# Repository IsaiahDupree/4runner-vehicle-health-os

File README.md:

# 4Runner Vehicle Health OS

Local-first, explainable vehicle-health and maintenance software for a 2005 Toyota 4Runner.

The project has two immutable source baselines: [Vehicle Health OS PRD v0.1](docs/prd/2005_Toyota_4Runner_Vehicle_Health_OS_PRD_v0.1.docx) and [Telemetry Build Master Spec v1](docs/prd/4Runner_Telemetry_Build_Master_Spec.docx). Their joined authority and unique requirement namespaces are defined in the [master project specification](docs/prd/MASTER-PROJECT-SPEC.md). The later [focused A/C telemetry source record](docs/prd/AC-TELEMETRY-SOURCE.md) controls the A/C node where it is more specific. The governing invariant is:

> raw observation -> decoded signal -> feature -> versioned equation -> calculation run -> finding -> recommendation -> service/inspection -> new lifecycle baseline

No derived value is authoritative unless that lineage can be reconstructed.

## Rev I lighting controller and voltage monitor

The [single-board Rev I hardware](hardware/console-led-node-v0.1/pcb-rgbw-revi/README.md)
adds protected ACC supply-voltage sensing to the existing six-wire Toyota inlet,
with revised native PCB, enclosure assembly, factory BOM and verification evidence.
The [WLED workspace](firmware/console-led-revg/CONFIGURATION.md) includes the actual
phone/head-unit UI, calibrated vehicle inputs and the existing CAN gateway's
foreground iPhone relay. It measures the switched feed at the box; ACC-off resting
battery monitoring is unavailable. Physical and vehicle qualification remain pending.

## Native iPhone lighting app

The [4Runner Lighting app](ios/Lighting/README.md) provides WLED-style color-wheel,
effect, segment and controller-preset controls. Config contains the existing CAN
relay, Rev I voltage monitor and Toyota input settings. It uses the current
single analog RGBW output zone.

The [4Runner WLED Integration skill](skills/4runner-wled-integration/SKILL.md)
preserves the approved interface, six-wire architecture, PCB/CAD and JLCPCB cost
lessons, with links to the actual test and delivery evidence.

## Rev H lighting controller

The [screw-terminal revision](hardware/console-led-node-v0.1/pcb-rgbw-revh/README.md)
uses one integrated PCB, six factory-soldered terminal blocks, a six-wire
Toyota inlet and a five-wire RGBW outlet. The gland-to-terminal wire paths,
support rails, fasteners and factory assembly files are included. It remains
an evaluation design requiring physical and vehicle qualification.

## Rev G media snapshot

The [single-board RGBW controller](hardware/console-led-node-v0.1/pcb-rgbw-revg/README.md)
includes the PCB, gland enclosure, inline Toyota power harness and WLED relay
integration. [Studio pictures and the narrated 3D demonstration](hardware/console-led-node-v0.1/pcb-rgbw-revg/presentation/README.md)
show its exterior, installed electronics, component layout and service assembly.
This is an evaluation prototype; physical electrical, sealing and vehicle-fit
acceptance remain pending.
[Download the video, CAD kits and 3D source](https://github.com/IsaiahDupree/4runner-vehicle-health-os/releases/tag/revg-studio-2026-11-21).

## Current baseline

E0 plus the first native iOS control slice are implemented here:

- stable typed domain IDs;
- versioned JSON Schemas for evidence, signals, captures, equations, calculations, and AI claims;
- a protobuf source contract and fixed transport-frame decision for mobile/ESP32 interoperability;
- deterministic simulator capture bundles with hashes and manifests;
- an A/C bench-sweep capture/replay path, A/C node telemetry and POST contracts, and evidence-bound pressure-lift, pressure-ratio, and vent-delta calculations;
- offline replay with integrity, sequence, timestamp, and schema validation;
- a versioned passive-CAN discovery analyzer that reports acquisition facts, sampling coverage,
  raw activity, checksum candidates, and correlations without assigning unverified vehicle meanings;
- a source-pinned 2005 4Runner passive-CAN hypothesis pack and real-corpus evaluator that exposes
  candidate fields, conflicting transforms, limitations, and validation gates while keeping the
  accepted signal count at zero;
- an immutable eight-session/5,176-record real-CAN replay corpus with SHA-256 provenance, clean and
  faulted live/history reconstruction, and production-decoder load tests in Python, Swift, and Kotlin;
- self-resynchronizing mobile stream decoders that surface discarded/corrupt transport bytes and
  recover later valid frames without converting communication faults into vehicle-health claims;
- a canonical 15-scenario real-evidence reliability matrix covering 20-cycle soak, MTU churn,
  bursts, duplicates, loss, corruption, reordering, stale link epochs, reconnects, modeled
  supervision timeout, queue overrun, bounded memory, and mixed interference, with aligned Swift
  transport tests and a full Kotlin/on-head-unit implementation;
- per-ECU SAE J1979 supported-PID enumeration, pinned standard read-only value decoding, and an
  iPhone/Android passive-response path that cannot substitute zero for unavailable evidence;
- synchronized Techstream/reference capture plus a candidate-only analyzer for `0x2C4`, `0x025`,
  and `0x2C1` raw fields;
- deterministic passive-CAN archive offload/reload plus an iOS multi-session research chart that
  plots retained evidence, pins pack/hash/validation lineage, and fails closed across app restarts;
- a durable iPhone private-evidence outbox and authenticated append-only receiver/agent claim queue;
- local checks for schema validity and deterministic replay;
- a Swift 6 core with CRC32C framing, guarded discovery plans, signed firmware verification, OTA preflight, and AI evidence handoff;
- a buildable native SwiftUI app with handshake-verified CoreBluetooth restoration,
  encrypted-bond reconnection, WiCAN factory detection, gateway health, signed semantic experiments,
  private-network OTA, and evidence export;
- a local-first technician diagnostic-case workspace with immutable revisions, typed evidence and
  hypotheses, hash-verified private attachments, verification/void history, and deterministic
  privacy-selected draft reports that cannot mutate canonical maintenance history;
- a signed public Release Hub consumed by iPhone and Android for target-aware Android, OBD ESP32,
  and A/C recovery artifact discovery and verified staging;
- a public WiCAN Pro ESP32-S3 firmware fork with passive/listen-only enforcement, framed BLE health reporting, OTA A/B partitions, and rollback self-tests;
- a physically targeted classic-ESP32/MrDIY firmware with bonded BLE health, passive CAN, persistent
  evidence, A/B rollback, a release-default-off status SoftAP, and explicitly activated signed Wi-Fi
  OTA;
- a backup-first public Web Serial provisioner with target detection, full-flash recovery download, release hashing, installation, and same-capacity restore;
- explicit iOS, legacy Android, gateway firmware, and added-sensor hardware boundaries.

No target-vehicle PID, threshold, service interval, or trim-specific constant is invented in this baseline. Those enter only through independently validated, versioned Vehicle Signal and Configuration Packs.

## Quick start

Requires Python 3.12 or newer.

```bash
python3 -m venv .venv
.venv/bin/python -m pip install -e './tooling[test]'
.venv/bin/vhos contracts check
.venv/bin/vhos simulate --scenario cold-start-idle --output build/captures/cold-start-idle
.venv/bin/vhos validate-bundle build/captures/cold-start-idle
.venv/bin/vhos replay build/captures/cold-start-idle
.venv/bin/vhos simulate --scenario ac-bench-sweep --output build/captures/ac-bench-sweep
.venv/bin/vhos validate-bundle build/captures/ac-bench-sweep
.venv/bin/vhos calculate-ac build/captures/ac-bench-sweep
.venv/bin/vhos discover-can path/to/passive-can-recent-logs.ndjson \
  --output build/can-discovery.report.json
.venv/bin/vhos evaluate-can-hypotheses \
  test-replay/real-can-2026-08-18/sessions \
  --output build/can-signal-hypotheses.report.json
.venv/bin/vhos validate-can-replay-corpus test-replay/real-can-2026-08-18
.venv/bin/vhos replay-can-corpus test-replay/real-can-2026-08-18 \
  --mode live --repeat 20 --fault clean
.venv/bin/vhos replay-can-corpus test-replay/real-can-2026-08-18 \
  --mode history --fault drop-fragment --fault-interval 257
.venv/bin/vhos test-link-reliability test-replay/real-can-2026-08-18 \
  --soak-cycles 20 --output build/link-reliability-matrix.json
.venv/bin/vhos decode-j1979 path/to/j1979-responses.ndjson \
  --supported-output build/j1979-supported.json \
  --samples-output build/j1979-standard-samples.ndjson
.venv/bin/vhos correlate-can-reference \
  --can path/to/passive-can.ndjson \
  --reference path/to/synchronized-reference-samples.csv \
  --output build/can-reference-candidates.json
.venv/bin/python -m pytest
```

The simulator namespace is deliberately separate from live vehicle data. It creates deterministic engineering evidence for automated tests; it never represents itself as a Toyota measurement.

## Gateway provisioning

- Signed release catalog: [VHOS Release Hub](https://github.com/IsaiahDupree/4runner-vhos-release-hub/releases/latest)
- Public installer: [VHOS Gateway Provisioner](https://vhos-gateway-provisioner.isaiahdupree.chatgpt.site)
- Public firmware source: [IsaiahDupree/4runner-vhos-firmware](https://github.com/IsaiahDupree/4runner-vhos-firmware)
- Development release and recovery evidence: [v0.1.0-dev.1](https://github.com/IsaiahDupree/4runner-vhos-firmware/releases/tag/v0.1.0-dev.1)
- Hardware/software baseline: [recommended hardware](docs/hardware/RECOMMENDED-HARDWARE.md) and [software baseline](docs/hardware/SOFTWARE-BASELINE.md)
- SoftAP incident and default-off activation decision: [2026-08-16 record](docs/development/ESP32-SOFTAP-ACTIVATION-INCIDENT-2026-08-16.md)
- One-command pre-car contracts/build/reset/app-death suite and true-power boundary: [BLE fault-injection plan](docs/development/BLE-FAULT-INJECTION-TEST-PLAN.md)
- Capture-export disconnect and dev28/dev29 recovery: [2026-08-18 incident](docs/development/BLE-CAPTURE-SYNC-DISCONNECT-INCIDENT-2026-08-18.md)

The first installation and recovery path uses a desktop Chrome or Edge browser, USB-C data, and Web
Serial. The browser requires a full-flash backup before it installs the merged image. The iPhone OTA
software path is implemented, but vehicle installation remains locked until deterministic PARKED
and gateway-supply evidence plus the physical backup/upload/power-loss/rollback/restore matrix pass.
See [iPhone to ESP32 Wi-Fi OTA](docs/development/IPHONE-TO-ESP32-WIFI-OTA.md).
The stable device labels and separation from transport identifiers are defined in
[the device naming contract](docs/development/DEVICE-NAMING-CONTRACT.md).

## Repository map

| Path | Responsibility |
| --- | --- |
| `docs/prd/` | Immutable product baseline and source integrity record |
| `docs/architecture/decisions/` | Accepted technical decisions and invariants |
| `contracts/jsonschema/v1/` | Authoritative serialized domain contracts |
| `contracts/proto/v1/` | Mobile/ESP32 payload source contract |
| `equations/v1/` | Immutable A/C equation definitions with applicability and truth boundaries |
| `tooling/` | Contract validator, simulator, bundle writer, and replay engine |
| `tests/` | Contract, determinism, corruption, ordering, and replay tests |
| `test-replay/` | Immutable real-capture corpora and cross-platform replay provenance |
| `ios/` | Native iOS app, portable Swift core, and deterministic XcodeGen project |
| `web-flasher/` | Public backup-first ESP32-S3 installer and recovery UI |
| `android/` | Preserved original Android module boundary; not the primary client after ADR-0003 |
| `firmware/` | Shared ESP32 component boundaries and read-only safety policy |
| `vehicle-signal-packs/` | Accepted signal/configuration packs plus separately contracted, discovery-only hypothesis packs that cannot feed owner health |

Related public repositories keep runtime ownership separate: Android head unit
[`4runner-vhos-android`](https://github.com/IsaiahDupree/4runner-vhos-android) ([download the current `0.1.0-dev.16` APK](https://github.com/IsaiahDupree/4runner-vhos-android/releases/download/android-v0.1.0-dev.16/app-debug.apk)), OBD firmware
[`4runner-vhos-firmware`](https://github.com/IsaiahDupree/4runner-vhos-firmware), A/C firmware
[`4runner-ac-telemetry-node`](https://github.com/IsaiahDupree/4runner-ac-telemetry-node), and the
signed catalog/portal [`4runner-vhos-release-hub`](https://github.com/IsaiahDupree/4runner-vhos-release-hub).

## Development order

1. E1: iOS append-only local truth store and lifecycle ledger; the gateway contract client is now scaffolded.
2. E2: physically verify the published WiCAN Pro VHOS foundation, then add passive capture and constrained discovery without widening the transmit boundary.
3. E3: iOS ingest, reconnect/deduplication, raw persistence, and replay adapter.
4. E4: verified generic OBD baseline plus target-vehicle signal discovery and validation.
5. E5/E6: maintenance schedule and equation/lineage engines before owner-facing scoring.

See [E0 implementation record](docs/delivery/E0-IMPLEMENTATION.md) for the exact backlog and acceptance mapping.
The current saved-vehicle evidence and strict UI interpretation boundary are recorded in the
[CAN discovery display baseline](docs/development/CAN-DISCOVERY-DISPLAY-BASELINE-2026-08-18.md).
The device-free sustained-load, corruption, fragmentation, disconnect, and Android historical
replay workflow is recorded in
[the real-CAN replay record](docs/development/REAL-CAN-REPLAY-AND-LOAD-TESTING-2026-08-18.md).
The 15-condition cross-device impairment matrix, acceptance budgets, Android reliability UI, and
remaining hardware-in-loop gates are recorded in
[the cross-device reliability lab](docs/development/CROSS-DEVICE-RELIABILITY-LAB-2026-08-18.md).
The supported-PID, synchronized Toyota-reference, and private-outbox implementation is recorded in
[the August 18 J1979/evidence delivery](docs/development/J1979-REFERENCE-VALIDATION-AND-PRIVATE-OUTBOX-2026-08-18.md).
The current source-pinned Toyota signal candidates, corpus results, interpretation boundaries, and
minimum validation session are recorded in
[the CAN signal interpretation record](docs/development/CAN-SIGNAL-INTERPRETATION-2026-08-18.md).
The latest iPhone-export verification, primary-source research update, candidate ranking, Android
display boundary, and next labeled-capture procedure are recorded in
[the 2026-08-20 CAN evidence and research update](docs/development/CAN-EVIDENCE-RESEARCH-UPDATE-2026-08-20.md).
The real-evidence iPhone chart, fresh-session archive reload gate, exact candidate fields, and
owner-health authority lock are recorded in
[the iOS retained CAN research implementation](docs/development/IOS-RETAINED-CAN-RESEARCH-GRAPHS-2026-08-20.md).
The play/pause/scrub/speed/loop transport, progressive exact-point graph, session-boundary display,
and real multi-session acceptance suite are recorded in
[the iOS retained CAN playback lab](docs/development/IOS-RETAINED-CAN-PLAYBACK-LAB-2026-08-20.md).

The authority-separated physical-unit candidates, derived statistics, rotational comparison, and
cross-platform presentation rules are recorded in [the CAN units view](docs/development/CAN-UNITS-NOTE-2026-08-28.md).

The authority boundary and delivered local iOS technician workflow are recorded in
[ADR-0005](docs/architecture/decisions/0005-technician-diagnostic-case-drafts.md) and the
[mechanic diagnostic-case implementation record](docs/development/MECHANIC-DIAGNOSTIC-CASE-MVP-2026-09-07.md).

Run the complete copied-iPhone evidence recovery, delta analysis, candidate
mapping, replay, and 15-scenario link stress lab with one command using
[the offline field-return runbook](docs/development/OFFLINE-FIELD-RETURN-ONE-SHOT.md).
Run that analysis together with all shared, Swift/iOS Simulator, and Android
desktop gates—without contacting any physical device—using
[the device-free field-return acceptance runner](docs/development/DEVICE-FREE-FIELD-RETURN-ACCEPTANCE.md).
The governing unknown-by-default whole-vehicle model, head-unit inventory contract, 2005 4Runner
configuration guard, and evidence-basis separation are recorded in
[the whole-vehicle digital-twin foundation](docs/development/WHOLE-VEHICLE-DIGITAL-TWIN-FOUNDATION-2026-08-18.md).
The cross-platform Connect → Discover → Test → Capture → Validate → Promote workflow, platform
roles, authority states, session records, fail-closed promotion gate, and first production slice are
defined in
[the Discovery subsystem architecture](docs/development/DISCOVERY-SUBSYSTEM-ARCHITECTURE-2026-08-21.md).
The Android vendor-stack discovery fallback, one-client iPhone/Android handoff, connected-launch
recovery, and explicitly owner-acknowledged local evidence-only selector workflow are recorded in
[the BLE/local-evidence runbook](docs/development/BLE-DISCOVERY-CONNECTED-LAUNCH-AND-LOCAL-EVIDENCE-2026-08-24.md).
The exact offline capture-finalization and experimental-candidate persistence boundary—and the
remaining reason the registration button stays disabled—are recorded in
[the offline candidate-registration gap](docs/development/OFFLINE-CANDIDATE-REGISTRATION-GAP-2026-08-24.md).

## Safety boundary

- Production gateway startup is passive/listen-only.
- There is no arbitrary CAN-transmit command in the shared contract.
- Any diagnostic request references a firmware-resident allowlist entry; iOS does not supply raw request bytes.
- Active Tests, vehicle control, ECU flashing, and code clearing are outside MVP scope.
- Gateway health/data loss is never presented as vehicle failure.

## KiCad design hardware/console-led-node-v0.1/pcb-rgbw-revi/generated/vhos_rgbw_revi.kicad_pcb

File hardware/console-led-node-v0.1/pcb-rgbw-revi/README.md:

# Rev I: protected switched-supply voltage sensing

Rev I adds on-board sensing of **ACC_FUSED**, after the main fuse and before the input eFuse. The same six-wire Toyota inlet remains the only power source. ACC-off resting battery measurements are unavailable. This is a voltage monitor for the supply at the box, not a state-of-charge meter or a battery-post measurement.

The existing SN3257-Q1 switch has unused channels. Channel 3 now connects VOLT_CLAMP at U5 pin 10 to VOLT_SW at pin 9 when CHIP_EN is valid; its alternate input stays grounded. The new path reuses the exact Rev H protected TAIL/DIM network and goes to ESP32-S3 GPIO1 / U11 pad 39. The remaining switch channel and the Toyota reserve wires stay unused.

| Added references | Existing part reused | Quantity |
|---|---|---:|
| R40, R41 | RT1206BRD0749K9L, 49.9k 0.1% | 2 |
| R42, R44 | 0603WAF2202T5E, 22k 1% | 2 |
| R43 | 0603WAF1802T5E, 18k 1% | 1 |
| U12 | LM4040C25QFTA, 2.5 V automotive shunt clamp | 1 |
| D10 | NSVBAT54HT1G, negative clamp | 1 |
| C32 | CC0603KRX7R9BB104, 100 nF 50 V | 1 |

This adds **eight populated positions, zero unique manufacturer SKUs**. At the retained November 21 JLCPCB snapshot, the material increment is **$0.8485**, making nominal PCB component material **$24.4326**. It is not a fresh checkout quote or finished-product price. Existing holder/clamp stock limitations, supplier assembly, fabrication, box build, firmware programming and testing remain separate. All parts are factory fitted.

The nominal ADC gain is 0.0684815; a 14.4 V input produces approximately 0.986 V at the ADC. A 32-corner resistor screen gives approximately 0.971–1.002 V, excluding switch, ADC, temperature and other errors. Firmware labels nominal conversion as an **uncalibrated estimate** until two meter-referenced bench points are applied. The shunt clamp saturates the transfer above its linear range; this is not a wide-range automotive pulse recorder.

[voltage_screen.py](voltage_screen.py) checks the actual selected manufacturer identities and resistor tolerances. Its clamp bounds are explicitly conditional assumptions inherited from the existing sensing design, not physical pulse evidence. Factory calibration, reset/isolation, negative-pulse behavior, resistor/clamp energy and voltage accuracy still need bench verification.

The accepted native Rev I board keeps the Rev H 133 x 65 mm outline, terminal locations and mounting positions, and adds the sensing parts in the existing free component area. Orion completed native routing with zero reported ERC, DRC, unconnected-net or schematic-parity findings under the retained project rules. The populated board passed 497 enclosure/wire checks, eight insert/driver access axes and three offline slices with supports disabled and zero support segments. The prior Rev H kit remains a separate frozen artifact.

| Revised artifact | File |
|---|---|
| Native PCB and schematic | [KiCad PCB](generated/vhos_rgbw_revi.kicad_pcb), [schematic PDF](generated/schematic.pdf) |
| Populated board geometry | [STEP](generated/routed_shield.step), [native board view](generated/board.png) |
| Complete enclosure assembly | [FreeCAD](generated/4Runner_RevI_Terminal_Assembly.FCStd), [STEP](generated/4Runner_RevI_Terminal_Assembly.step) |
| Support-free print exports | [Base STL](generated/case_base.stl), [lid STL](generated/case_lid.stl), [gland plate STL](generated/gland_plate.stl) |
| Factory assembly | [75-position BOM](jlcpcb/BOM.csv), [placement CPL](jlcpcb/CPL.csv), [Gerbers](generated/4Runner_RGBW_RevI_Gerbers.zip) |
| Wiring and provenance | [Wire register](WIRE-REGISTER.csv), [routing lengths](generated/wire-cut-routing.csv), [native verification](generated/verification.json), [test evidence](VERIFICATION.md) |

The complete product still needs the unchanged [harness and case hardware](../pcb-rgbw-revh/HARNESS-AND-CASE.csv), external inline harness and supplier box assembly/programming/testing. A BOM/CPL is factory input; it is not confirmation of JLCPCB stock, through-hole assembly acceptance or a delivered plug-and-play quote.

Software and UI behavior: [WLED/CAN/vehicle-input configuration](../../../firmware/console-led-revg/CONFIGURATION.md). Rev I firmware enables GPIO1 sense; the unmodified Rev H board must use the original target without that input.

This revision is evaluation hardware. No physical installation or manufacturing release is implied by source, static screening, a successful firmware build or digital fit checks.

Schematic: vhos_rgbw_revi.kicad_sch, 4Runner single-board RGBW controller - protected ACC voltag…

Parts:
C2, C3, C30: 2.2u 100V X7R; C_1210_3225Metric; MPN CL32B225KCJVPJE
C4: 10n 50V X7R; C_0603_1608Metric; MPN 0603B103K500NT
C13, C27, C29: 100n 100V X7R; C_0805_2012Metric; MPN CL21B104KCFNNNE
C17: 47u 50V; CP_Elec_8x6.2; MPN EEEFK1H470P
C18, C19, C20, C32: 100n 50V; C_0603_1608Metric; MPN CC0603KRX7R9BB104
C22, C23, C24, C31: 22u 25V X5R; C_1206_3216Metric; MPN CL31A226KAHNNNE
C25, C28: 100n 50V X7R; C_0603_1608Metric; MPN CC0603KRX7R9BB104
C26: 1u 50V X5R; C_0603_1608Metric; MPN CL10A105KB8NNNC
D1, D2: SMBJ28CAQ; D_SMB; MPN SMBJ28CAQ-13-F
D7, D8, D10: NSVBAT54HT1G; onsemi_SOD-323_477; MPN NSVBAT54HT1G
D9: SS56 60V 5A; D_SMA; MPN SS56
F1: 3A MINI MAIN / LED; Keystone_3568_MINI_Vertical; MPN 3568-10
F2: 1A MINI LOGIC; Keystone_3568_MINI_Vertical; MPN 3568-10
JT1: GND/ACC; KEFA_KF128_5.08_2P; MPN KF128-5.08-2P-AA
JT2: TAIL/DIM; KEFA_KF128_5.08_2P; MPN KF128-5.08-2P-AA
JT3: RSV3/RSV4; KEFA_KF128_5.08_2P; MPN KF128-5.08-2P-AA
JT4: R-/G-; KEFA_KF128_5.08_2P; MPN KF128-5.08-2P-AA
JT5: B-/+LED; KEFA_KF128_5.08_2P; MPN KF128-5.08-2P-AA
JT6: W-/NC; KEFA_KF128_5.08_2P; MPN KF128-5.08-2P-AA
L1: 22u 20% TDK; TDK_SPM6545VT-D; MPN SPM6545VT-220M-D
MH1, MH2, MH3, MH4: M3 CASE SUPPORT; MountingHole_3.2mm_M3; MPN PCB FEATURE
Q1: AO3400A; SOT-23; MPN AO3400A
R1: 8.2k 1%; R_0603_1608Metric; MPN 0603WAF8201T5E
R2, R5: 47k 1%; R_0603_1608Metric; MPN 0603WAF4702T5E
R3, R13: 10k 1%; R_0603_1608Metric; MPN 0603WAF1002T5E
R4: 150k 1%; R_0603_1608Metric; MPN 0603WAF1503T5E
R17, R18, R19, R20: 100k; R_0603_1608Metric; MPN 0603WAF1003T5E
R21: 46.4k 0.1%; R_0603_1608Metric; MPN RT0603BRD0746K4L
R22: 3.92k 0.1%; R_0603_1608Metric; MPN RT0603BRD073K92L
R24, R25, R26, R27, R40, R41: 49.9k 0.1%; R_1206_3216Metric; MPN RT1206BRD0749K9L
R28, R29, R32, R33, R42, R44: 22k 1%; R_0603_1608Metric; MPN 0603WAF2202T5E
R30, R31, R43: 18k 1%; R_0603_1608Metric; MPN 0603WAF1802T5E
R36, R37, R38: 10k; R_0603_1608Metric; MPN 0603WAF1002T5E
R39: 100k 1%; R_0603_1608Metric; MPN 0603WAF1003T5E
TP5: LED_POS; TestPoint_Pad_D1.0mm; MPN PCB FEATURE
TP6: GND; TestPoint_Pad_D1.0mm; MPN PCB FEATURE
TP7: VIN_PROT; TestPoint_Pad_D1.0mm; MPN PCB FEATURE
TP8: ENABLE_REQ; TestPoint_Pad_D1.0mm; MPN PCB FEATURE
TP9: GND; TestPoint_Pad_D1.5mm; MPN PCB FEATURE
TP10: UART_TX; TestPoint_Pad_D1.5mm; MPN PCB FEATURE
TP11: UART_RX; TestPoint_Pad_D1.5mm; MPN PCB FEATURE
TP12: BOOT_N; TestPoint_Pad_D1.5mm; MPN PCB FEATURE
TP13: CHIP_EN; TestPoint_Pad_D1.5mm; MPN PCB FEATURE
TP14: ESP_3V3; TestPoint_Pad_D1.5mm; MPN PCB FEATURE
U1: LMR51610XDBVR; SOT-23-6; MPN LMR51610XDBVR
U2: DRV8803PWPR; TI_PWP0016J; MPN DRV8803PWPR
U4: TPS26600PWPR; TI_PWP0016A; MPN TPS26600PWPR
U5: SN3257-Q1; TSSOP-16_4.4x5mm_P0.65mm; MPN SN3257QPWRQ1
U6, U7, U12: LM4040 2.5V; SOT-23; MPN LM4040C25QFTA
U10: TLV803EC30DBZR; SOT-23; MPN TLV803EC30DBZR
U11: ESP32-S3-WROOM-1-N16R2; ESP32-S3-WROOM-1; MPN ESP32-S3-WROOM-1-N16R2

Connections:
/ACC_FUSED: C13.1, C30.1, D1.1, F1.2, R2.1, R21.1, R40.1, U4.1 (IN), U4.2 (IN)
/BOOTCAP: C28.1, U1.1 (CB)
/BOOT_N: R37.2, TP12.1, U11.27 (IO0)
/CHIP_EN: C26.1, R36.2, TP13.1, U5.1 (SEL), U10.1 (RESET_N), U11.3 (EN)
/DIM_ADC: C20.1, R31.2, R33.1, U11.4 (IO4)
/DIM_CLAMP: D8.1 (K), R27.2, R29.1, U5.6 (S2B), U7.1 (K)
/DIM_RETURN: JT2.2 (DIM), R26.1
/DIM_SERIES: R26.2, R27.1
/DIM_SW: R31.1, U5.7 (D2)
/DOWNLOAD_STRAP: R38.1, U11.16 (IO46)
/EFUSE_RTN: C4.2, R1.2, R3.2, R22.2, U4.6 (MODE), U4.8 (RTN), U4.17 (EPAD)
/ENABLE_REQ: Q1.1 (G), R39.1, TP8.1, U11.23 (IO21)
/ESP_3V3: C18.1, C22.1, C23.1, C24.1, C25.1, C31.1, L1.2, R4.1, R13.1, R36.1, R37.1, TP14.1, U5.16 (VDD), U10.3 (VDD), U11.2 (3V3)
/FB_3V3: R4.2, R5.1, U1.3 (FB)
/GND: C2.2, C3.2, C13.2, C17.2, C18.2, C19.2, C20.2, C22.2, C23.2, C24.2, C25.2, C26.2, C27.2, C29.2, C30.2, C31.2, C32.2, D1.2, D2.2, D7.2 (A), D8.2 (A), D9.2, D10.2 (A), JT1.1 (GND), Q1.2 (S), R5.2, R17.2, R18.2, R19.2, R20.2, R28.2, R29.2, R32.2, R33.2, R38.2, R39.2, R42.2, R44.2, TP6.1, TP9.1, U1.2 (GND), U2.5 (GND), U2.9 (RESET), U2.12 (GND), U2.17 (EPAD), U4.9 (GND), U5.2 (S1A), U5.5 (S2A), U5.8 (GND), U5.11 (S3A), U5.12 (D4), U5.13 (S4B), U5.14 (S4A), U5.15 (EN_N), U6.2 (A), U6.3 (A/NC), U7.2 (A), U7.3 (A/NC), U10.2 (GND), U11.1 (GND), U11.40 (GND), U11.41 (EPAD), U12.2 (A), U12.3 (A/NC)
/ILIM: R1.1, U4.11 (ILIM)
/LED_B_NEG: JT5.1 (B-), U2.6 (OUT3)
/LED_EN_N: Q1.3 (D), R13.2, U2.8 (NENBL)
/LED_G_NEG: JT4.2 (G-), U2.4 (OUT2)
/LED_POS: C17.1, C27.1, D2.1, D9.1, F2.1, JT5.2 (+LED), TP5.1, U2.1 (VM), U2.2 (VCLAMP), U4.15 (OUT), U4.16 (OUT)
/LED_R_NEG: JT4.1 (R-), U2.3 (OUT1)
/LED_W_NEG: JT6.1 (W-), U2.7 (OUT4)
/OVP: R21.2, R22.1, U4.5 (OVP)
/PWM_B: R19.1, U2.11 (IN3), U11.22 (IO14)
/PWM_G: R18.1, U2.13 (IN2), U11.10 (IO17)
/PWM_R: R17.1, U2.14 (IN1), U11.11 (IO18)
/PWM_W: R20.1, U2.10 (IN4), U11.38 (IO2)
/SLEW: C4.1, U4.12 (DVDT)
/SW: C28.2, L1.1, U1.6 (SW)
/TAIL_12V: JT2.1 (TAIL), R24.1
/TAIL_ADC: C19.1, R30.2, R32.1, U11.5 (IO5)
/TAIL_CLAMP: D7.1 (K), R25.2, R28.1, U5.3 (S1B), U6.1 (K)
/TAIL_SERIES: R24.2, R25.1
/TAIL_SW: R30.1, U5.4 (D1)
/UART_RX: TP11.1, U11.36 (RXD0)
/UART_TX: TP10.1, U11.37 (TXD0)
/UVLO: R2.2, R3.1, U4.3 (UVLO)
/VEH_ACC: F1.1, JT1.2 (ACC)
/VIN_PROT: C2.1, C3.1, C29.1, F2.2, TP7.1, U1.4 (EN), U1.5 (VIN)
/VOLT_ADC: C32.1, R43.2, R44.1, U11.39 (IO1)
/VOLT_CLAMP: D10.1 (K), R41.2, R42.1, U5.10 (S3B), U12.1 (K)
/VOLT_SERIES: R40.2, R41.1
/VOLT_SW: R43.1, U5.9 (D3)

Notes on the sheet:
FUSED INPUT, REVERSE / SURGE PROTECTION AND 3.3 V SUPPLY
TOYOTA IR1 INPUT, RGBW OUTPUT AND TEST PADS
ONE COMMON-POSITIVE RGBW ZONE
TOYOTA IR1 ILLUMINATION SENSE
ONBOARD ESP32-S3, 3.3 V REGULATOR AND SERVICE PADS
EVALUATION HARDWARE / VERIFY VEHICLE FEED, LED PINOUT AND USB ISOLATION

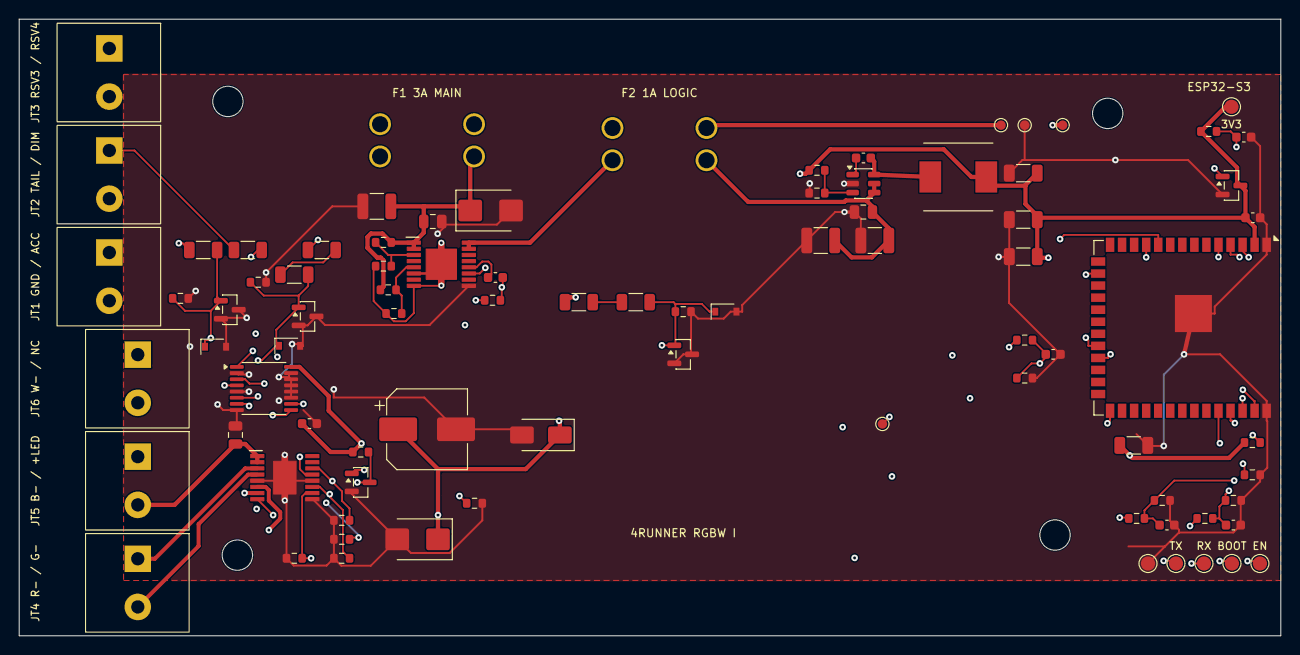
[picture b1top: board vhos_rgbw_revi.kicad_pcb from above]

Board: 4 copper layers, 133.0 x 65.0 mm, 89 parts (0 on the bottom side), 43 nets.

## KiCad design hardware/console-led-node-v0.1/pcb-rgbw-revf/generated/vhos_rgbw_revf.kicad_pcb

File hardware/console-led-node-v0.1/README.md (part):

# 2005 V8 4Runner console LED node — research and fit-check case

**Current build** [Rev G single-board controller and harness](pcb-rgbw-revg/README.md).
The photographed white six-contact Toyota harness is the box's only wired
input. The shield uses that switched 12 V and ground to power both the
ESP32-S3 and the RGBW lights. Two protected inputs read the TAIL and dimmer
circuits through the same harness. IR1-3 and IR1-4 have labeled, capped tails
at the external tee. The existing ESP32/MrDIY gateway supplies vehicle data
wirelessly. [Wire register](pcb-rgbw-revg/WIRE-REGISTER.csv).
[Project resources and fabrication files](RESOURCES.md).
Owner task: 2026-11-07. No parts ordered, functional PCB fabricated, vehicle wiring changed, or printer started.

The [earlier two-connector Rev B package](pcb-rgbw-revb/README.md) places both replaceable
fuses, reverse-battery and overvoltage protection, regulated ESP32 power and
the RGBW output on the shield. It uses one switched vehicle input and one
five-wire LED cable at the case. Its assembly instructions document that earlier population.

The earlier [RGBW Rev A package](pcb-rgbw-reva/README.md) supplies native KiCad
files, four PWM power channels, a protected logic-supply draft, a BOM and
updated case parts. Its final Orion export has zero ERC/DRC findings and zero
unfinished connections. Nominal CAD interference checks pass for the revised
assembly. The [Rev A inline harness build sheet](connector-adapter/INLINE-HARNESS.md)
retains the Toyota pass-through and earlier shield wiring. The vehicle feed,
connector fit, pod pinout, controller stack and RF fit still need physical verification.

The connector research and original inline harness record earlier evaluation
revisions. Use the current build guide for wiring the box.

## What the photographs establish

| Location | Observation and working identification | Remaining check |
| --- | --- | --- |
| Black cylindrical component at upper left | Rear of a cigarette-lighter / 12 V socket assembly | Strong visual identification; distinguish the actual socket variant by its label and front view |
| Beige connector beside that socket | Part of the local socket/illumination wiring | Function inferred from its physical routing; cavity count, mating face and part number unreadable |
| Loose white plug at lower left | Six-contact socket in the Yazaki **7283-1060** pattern. The catalog mate is **7282-1060**. Location and colors match the documented **IR1** loom | Confirm latch fit, cavity markings and electrical behavior on the truck |
| Blue connector in black switch housing at right | A console switch connection | Exact switch unidentified without its front legend; no assertion that it is DAC, differential lock or another trim-specific function |

Toyota's 2005 V8 service diagrams identify IR1 as the join between the
instrument-panel wiring and the cigarette-lighter wiring assembly. The
connector list separately identifies C6 lighter housing **90980-10760**
and C7 lamp housing **90980-11148** at the components. The photographs and
diagram support the IR1 identification. The housing fit and live ACC feed
still need checking on the truck. [IR1 pinout and harness plan](connector-adapter/IR1-WIRE-PLAN.md) ·
[Toyota connector list][ewd-connectors] · [Toyota TIS][tis].

Compare the actual mating face, latch and cavities when ordering the
pass-through parts. Match circuits by physical terminal alignment and
continuity during assembly.

## Parts that can be sourced

The complete candidate list, quantities and unresolved selection conditions are
in [BOM.csv](BOM.csv). All electronic parts are research candidates, not a
released fabrication BOM.

The [connector-to-shield research](connector-adapter/README.md) supplies the
Yazaki mating pair, the Molex PCB interface and official UNO R3 header
coordinates. The [inline harness parts list](connector-adapter/INLINE-HARNESS.md#parts)
covers the earlier Rev A cable build.

The subsequent [component CAD collection](cad-references/README.md) records six
downloaded STEP references, manufacturer versus community provenance, native
Orion inspection and the remaining Toyota/full-controller model gaps.

| Item | Concrete lead | What it establishes |
| --- | --- | --- |
| Console wiring assembly | **Toyota 82390-35010** | Dealer calls it Bulb Wire / Wiring Assembly Cigaret, center console. ToyotaPartsDeal lists 4.7 L 2UZ-FE compatibility. It may be only part of the lamp/socket loom; terminal population and both ends require a real product photo. [Dealer listing][toyota-harness], [secondary availability][harness-sale] |
| OEM socket housing | **Toyota 90980-10760** | Female housing cataloged for the lighter; not the identified mate for the loose multi-pin plug. Secondary listing currently says unavailable. [Listing][socket-housing] |
| Locking PCB connector | **Molex 43045-0600** | Six-circuit, 3 mm pitch, right-angle through-hole Micro-Fit header with PCB retention. [Manufacturer][molex-header] |
| Matching cable housing / contacts | **43025-0600 + 43030-0007** | Matching Micro-Fit family, 20–24 AWG tin socket contacts; verify insulation OD ≤1.85 mm and use the proper crimp tool. This pair fits our PCB, not Toyota's loom directly. [Housing][molex-housing], [contacts][molex-contact], [family mating catalog][molex-family] |
| Protected 5 V supply | **LM5164-Q1** | 6–100 V input, 1 A buck candidate for controller/logic. Supporting components, thermal behavior and cranking recovery remain design work. [TI][buck] |
| Reverse-battery protection | **LM74700-Q1 + suitable external N-FET** | Ideal-diode controller candidate, not a complete load-dump solution. Clamp, surge energy, FET and fuse must be designed together. [TI][ideal-diode] |
| Addressable LED data option | **SN74AHCT125-Q1** | 5 V buffer with TTL-compatible input; a possible 3.3-to-5 V data stage, not an LED power supply. [TI][level-shifter] |
| 12 V analog RGB option | **UCC27524A-Q1 + BUK9K12-60E** | Gate-driver and dual 60 V N-FET candidates; a three-channel RGB load needs enough channels, separate fusing and a reviewed thermal/current design. [TI][gate-driver], [Nexperia][mosfet] |
| Printed-case hardware | **8 × ruthex RX-M3x5.7**, **4 × M3x8**, **4 × M3x6 + insulating washers** | Case/own-carrier mounting only; not verified UNO mounting holes. [Insert manufacturer][inserts] |

Observed quotations on the research date: the Toyota wiring assembly was
$20.78 at Olathe and $14.86 with a stated 1–3 business day dispatch at
ToyotaPartsDeal. These are page observations, excluding delivery/tax and
subject to seller/VIN confirmation. No purchase has been placed.

The [earlier placement preview](pcb-preview/README.md) is superseded by the
[routed RGBW draft and native preview](pcb-rgbw-reva/README.md).

The subsequent [underbody LED comparison](led-selection/README.md) evaluates
sealed rock-light pods and an addressable strip against the owner's outdoor
mounting requirement. It recommends a DD7440 RGBW sample for evaluation; the
light and interface remain unselected. RGBW requires four power channels per
independent zone, so the earlier three-channel RGB or data-output concept is
not a final output circuit.

## Electrical and mechanical arrangement

The [Rev G bench and programming guide](pcb-rgbw-revg/BENCH.md)
covers the onboard ESP32-S3 and the 3.3 V regulator. The [Rev D two-board build](pcb-rgbw-revd/README.md)
and [shared Toyota power flow](pcb-rgbw-revb/TOYOTA-POWER-BUILD.md#power-and-lighting-leads)
record the earlier stacked version.
Check the Toyota power and ground cavities and the available current on the
truck. The case supports both captive cables at their exits.

The user identified the stacked version's controller with a product screenshot:
**ShengYang listing, purple D1 UNO ESP32-S3 N16R8 / CH340 board**. The earlier
DIYables brand assumption is superseded. Its visible UNO-style header layout
and GPIO labels agree with the seller-family reference. The new
[board identity and shield GPIO proposal](controller-board/README.md) records
that evidence, the seller dimension drawing and 32 header positions.
GPIO is a 3.3 V domain; the printed 5 V/IOREF and RST/AREF positions are not an
AVR UNO electrical pinout. Exact populated height, hole positions, power-path
behavior and final physical fit remain unverified. The original case inputs
and receipts remain frozen, with their estimated controller envelope.

The existing VHOS repository already preserves raw observations and signal
quality. Its README reports zero accepted target-specific passive-CAN signals
for the hypothesis pack. Do not turn candidate CAN bytes into RPM, temperature,
door-state or fault claims. Standard OBD responses also require actual
per-ECU supported-PID evidence. This package adds no firmware, signal decoding,
CAN transmission, vehicle actuation or app control service.

For a first implementation, the existing iPhone/head-unit client can read the
gateway and send bounded LED commands to a second BLE peripheral. That link is
**proposed, not implemented**. A direct ESP32-to-gateway link needs the gateway's
actual service/connection capacity and radio coexistence validated; a second
BLE client cannot be assumed to coexist with the current app. iOS uses BLE,
not an assumed classic Bluetooth serial connection. Wi-Fi requires an explicit
local session; do not turn on the existing default-off gateway SoftAP silently.

Only fresh, validated measurements may drive a configured rule. Boot,
disconnection, stale or invalid data must set a documented safe LED state;
unknown must not mean “zero” or a green vehicle-health indication. Use hardware
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
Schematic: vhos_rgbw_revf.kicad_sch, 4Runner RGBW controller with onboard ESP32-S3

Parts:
C1: 10u 63V EEEFK1J100P; CP_Elec_6.3x5.8; MPN EEEFK1J100P
C2, C3: 2.2u 100V X7R; C_1210_3225Metric; MPN CL32B225KCJVPJE
C4: 2.2n 50V X7R; C_0603_1608Metric; MPN 0603B222K500NT
C5: 3.3n 50V X7R; C_0603_1608Metric; MPN CL10B332KB8NNNC
C6: 180p C0G; C_0603_1608Metric; MPN CL10C181JB8NNNC
C7, C8: 22u 25V X7R; C_1210_3225Metric; MPN MCAST32MSB7226KPNA01
C9, C11: 100n 25V X7R; C_0603_1608Metric; MPN CC0603KRX7R9BB104
C10, C12, C26: 1u 25V X7R; C_0603_1608Metric; MPN CL10B105KA8NNNC
C13, C14: 100n 100V X7R; C_0805_2012Metric; MPN CL21B104KCFNNNE
C15, C25: 100n 50V X7R; C_0603_1608Metric; MPN CC0603KRX7R9BB104
C16: 10n 100V X7R; C_0805_2012Metric; MPN GRM21BR72A103KA01L
C17: 47u 50V; CP_Elec_8x6.2; MPN EEEFK1H470P
C18, C19, C20, C21: 100n 50V; C_0603_1608Metric; MPN CC0603KRX7R9BB104
C22, C23, C24: 22u 16V X7R; C_1206_3216Metric; MPN EMK316BB7226ML-T
D1: SMBJ28CAQ; D_SMB; MPN SMBJ28CAQ-13-F
D3, D4, D5, D6: SMBJ24CA; D_SMB; MPN SMBJ24CAQ-13-F
D7, D8: NSVBAT54HT1G; onsemi_SOD-323_477; MPN NSVBAT54HT1G
F1: 3A MINI MAIN / LED; Keystone_3568_MINI_Vertical; MPN 3568
F2: 1A MINI LOGIC; Keystone_3568_MINI_Vertical; MPN 3568
J1: TOYOTA IR1 IN; Toyota_IR1_4_Pads
J2: RGBW OUT; RGBW_Output_5_Pads
L1: 68u 20% TDK; TDK_SPM6545VT-D; MPN SPM6545VT-680M-D
L2: 2.2uH; L_Bourns-SRN4018; MPN SRN4018-2R2M
MH1, MH2, MH3, MH4: M3 CASE SUPPORT; MountingHole_3.2mm_M3; MPN PCB FEATURE
Q1, Q2, Q3, Q4: BUK9Y15-60E; LFPAK56; MPN BUK9Y15-60E,115
Q5, Q6: BUK9Y19-100E; LFPAK56; MPN BUK9Y19-100E,115
R1: 39k 1%; R_0603_1608Metric; MPN 0603WAF3902T5E
R2: 1M; R_0603_1608Metric; MPN 0603WAF1004T5E
R3: 220k 1%; R_0603_1608Metric; MPN 0603WAF2203T5E
R4: 150k 1%; R_0603_1608Metric; MPN 0603WAF1503T5E
R5: 47k 1%; R_0603_1608Metric; MPN 0603WAF4702T5E
R6: 68k 1%; R_0603_1608Metric; MPN 0603WAF6802T5E
R7, R17, R18, R19, R20: 100k; R_0603_1608Metric; MPN 0603WAF1003T5E
R8: 2.2k; R_0603_1608Metric; MPN 0603WAF2201T5E
R9, R10, R11, R12: 100; R_0603_1608Metric; MPN 0603WAF1000T5E
R13, R14, R15, R16, R36, R37, R38: 10k; R_0603_1608Metric; MPN 0603WAF1002T5E
R21, R34: 46.4k 0.1%; R_0603_1608Metric; MPN RT0603BRD0746K4L
R22: 4.02k 0.1%; R_0603_1608Metric; MPN RT0603BRD074K02L
R23: 100R; R_0603_1608Metric; MPN 0603WAF1000T5E
R24, R25, R26, R27: 49.9k 0.1%; R_1206_3216Metric; MPN RT1206BRD0749K9L
R28, R29, R32, R33: 22k 0.1%; R_0603_1608Metric; MPN AT0603BRD0722KL
R30, R31: 18k 1%; R_0603_1608Metric; MPN 0603WAF1802T5E
R35: 10k 1%; R_0603_1608Metric; MPN 0603WAF1002T5E
TP5: V5_LOGIC; TestPoint_Pad_D1.0mm; MPN PCB FEATURE
TP6: GND; TestPoint_Pad_D1.0mm; MPN PCB FEATURE
TP7: PGOOD; TestPoint_Pad_D1.0mm; MPN PCB FEATURE
TP8: ENABLE_REQ; TestPoint_Pad_D1.0mm; MPN PCB FEATURE
TP9: GND; TestPoint_Pad_D1.5mm; MPN PCB FEATURE
TP10: UART_TX; TestPoint_Pad_D1.5mm; MPN PCB FEATURE
TP11: UART_RX; TestPoint_Pad_D1.5mm; MPN PCB FEATURE
TP12: BOOT_N; TestPoint_Pad_D1.5mm; MPN PCB FEATURE
TP13: CHIP_EN; TestPoint_Pad_D1.5mm; MPN PCB FEATURE
TP14: ESP_3V3; TestPoint_Pad_D1.5mm; MPN PCB FEATURE
U1: LM5164QDDARQ1; HSOP-8-1EP_3.9x4.9mm_P1.27mm_EP2.41x3.1mm; MPN LM5164QDDARQ1
U2, U3: UCC27524AQDRQ1; SOIC-8_3.9x4.9mm_P1.27mm; MPN UCC27524AQDRQ1
U4: LM74800-Q1; WSON-12-1EP_3x3mm_P0.5mm_EP1.5x2.5mm; MPN LM74800QDRRRQ1
U5: SN3257-Q1; TSSOP-16_4.4x5mm_P0.65mm; MPN SN3257QPWRQ1
U6, U7: LM4040 2.5V; SOT-23; MPN LM4040C25QFTA
U8: TLV809E 2.93V; SOT-23; MPN TLV809ED29DBZR
U9: TLV62569DBVR; SOT-23-5; MPN TLV62569DBVR
U10: TLV803EC30DBZR; SOT-23; MPN TLV803EC30DBZR
U11: ESP32-S3-WROOM-1-N16R8; ESP32-S3-WROOM-1; MPN ESP32-S3-WROOM-1-N16R8

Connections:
/ACC_FUSED: C13.1, D1.1, F1.2, Q5.1, Q5.2, Q5.3, U4.2 (A), U4.3 (VSNS)
/BOOT_N: R37.2, TP12.1, U11.27 (IO0)
/BST: C4.1, U1.7 (BST)
/CAP_PUMP: C15.1, U4.11 (CAP)
/CHIP_EN: C26.1, R36.2, TP13.1, U10.1 (RESET_N), U11.3 (EN)
/DGATE: Q5.4, U4.1 (DGATE)
/DIM_ADC: C20.1, R31.2, R33.1, U11.4 (IO4)
/DIM_CLAMP: D8.1 (K), R27.2, R29.1, U5.6 (S2B), U7.1 (K)
/DIM_RETURN: J1.4 (IR1-2), R26.1
/DIM_SERIES: R26.2, R27.1
/DIM_SW: R31.1, U5.7 (D2)
/DOWNLOAD_STRAP: R38.1, U11.16 (IO46)
/DRV_B: R11.1, U3.7 (OUTA)
/DRV_G: R10.1, U2.5 (OUTB)
/DRV_R: R9.1, U2.7 (OUTA)
/DRV_W: R12.1, U3.5 (OUTB)
/ENABLE_REQ: R8.1, TP8.1, U2.1 (ENA), U2.8 (ENB), U3.1 (ENA), U3.8 (ENB), U11.23 (IO21)
/ESP_3V3: C18.1, C21.1, C23.1, C24.1, C25.1, L2.2, R34.1, R36.1, R37.1, TP14.1, U5.16 (VDD), U8.3 (VDD), U10.3 (VDD), U11.2 (3V3)
/FB: C6.2, R4.2, R5.1, U1.5 (FB)
/FB_3V3: R34.2, R35.1, U9.5 (FB)
/GATE_B: Q3.4 (G), R11.2, R15.1
/GATE_G: Q2.4 (G), R10.2, R14.1
/GATE_R: Q1.4 (G), R9.2, R13.1
/GATE_W: Q4.4 (G), R12.2, R16.1
/GND: C1.2, C2.2, C3.2, C7.2, C8.2, C9.2, C10.2, C11.2, C12.2, C13.2, C14.2, C16.2, C17.2, C18.2, C19.2, C20.2, C21.2, C22.2, C23.2, C24.2, C25.2, C26.2, D1.2, D3.2, D4.2, D5.2, D6.2, D7.2 (A), D8.2 (A), J1.1 (IR1-5), Q1.1 (S1), Q1.2 (S2), Q1.3 (S3), Q2.1 (S1), Q2.2 (S2), Q2.3 (S3), Q3.1 (S1), Q3.2 (S2), Q3.3 (S3), Q4.1 (S1), Q4.2 (S2), Q4.3 (S3), R1.2, R3.2, R5.2, R8.2, R13.2, R14.2, R15.2, R16.2, R17.2, R18.2, R19.2, R20.2, R22.2, R28.2, R29.2, R32.2, R33.2, R35.2, R38.2, TP6.1, TP9.1, U1.1 (GND), U1.9 (EP_GND), U2.3 (GND), U3.3 (GND), U4.7 (GND), U5.2 (S1A), U5.5 (S2A), U5.8 (GND), U5.9 (D3), U5.10 (S3B), U5.11 (S3A), U5.12 (D4), U5.13 (S4B), U5.14 (S4A), U5.15 (EN_N), U6.2 (A), U6.3 (A/NC), U7.2 (A), U7.3 (A/NC), U8.2 (GND), U9.2 (GND), U10.2 (GND), U11.1 (GND), U11.40 (GND), U11.41 (EPAD)
/HGATE: Q6.4, R23.1, U4.8 (HGATE)
/INRUSH: C16.1, R23.2
/LED_B_NEG: D5.1, J2.3, Q3.5 (D_MB)
/LED_G_NEG: D4.1, J2.2, Q2.5 (D_MB)
/LED_POS: C17.1, F2.1, J2.4, Q6.1, Q6.2, Q6.3, U4.9 (OUT)
/LED_R_NEG: D3.1, J2.1, Q1.5 (D_MB)
/LED_W_NEG: D6.1, J2.5, Q4.5 (D_MB)
/OV_FEED: R21.1, U4.4 (SW)
/OV_SENSE: R21.2, R22.1, U4.5 (OV)
/PGOOD: R7.2, TP7.1, U1.6 (PGOOD)
/POWER_MID: C14.1, C15.2, Q5.5, Q6.5, U4.6 (EN/UVLO), U4.10 (VS), U4.12 (C)
/PWM_B: R19.1, U3.2 (INA), U11.22 (IO14)
/PWM_G: R18.1, U2.4 (INB), U11.10 (IO17)
/PWM_R: R17.1, U2.2 (INA), U11.11 (IO18)
/PWM_W: R20.1, U3.4 (INB), U11.38 (IO2)
/RIPPLE: C5.1, C6.1, R6.2
/RON: R1.1, U1.4 (RON)
/SENSE_READY: U5.1 (SEL), U8.1 (RESET_N)
/SW: C4.2, L1.1, R6.1, U1.8 (SW)
/SW_3V3: L2.1, U9.3 (SW)
/TAIL_12V: J1.3 (IR1-1), R24.1
/TAIL_ADC: C19.1, R30.2, R32.1, U11.5 (IO5)
/TAIL_CLAMP: D7.1 (K), R25.2, R28.1, U5.3 (S1B), U6.1 (K)
/TAIL_SERIES: R24.2, R25.1
/TAIL_SW: R30.1, U5.4 (D1)
/UART_RX: TP11.1, U11.36 (RXD0)
/UART_TX: TP10.1, U11.37 (TXD0)
/UVLO: R2.2, R3.1, U1.3 (EN_UVLO)
/V5_LOGIC: C5.2, C7.1, C8.1, C9.1, C10.1, C11.1, C12.1, C22.1, L1.2, R4.1, R7.1, TP5.1, U2.6 (VDD), U3.6 (VDD), U9.1 (EN), U9.4 (VIN)
/VEH_ACC: F1.1, J1.2 (IR1-6)
/VIN_PROT: C1.1, C2.1, C3.1, F2.2, R2.1, U1.2 (VIN)

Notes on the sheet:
FUSED INPUT, PROTECTION AND 5 V SUPPLY
VEHICLE INPUT AND CONTROLLER STACK
ONE COMMON-POSITIVE RGBW ZONE
TOYOTA IR1 ILLUMINATION SENSE
ONBOARD ESP32-S3, 3.3 V REGULATOR AND SERVICE PADS
EVALUATION HARDWARE / VERIFY VEHICLE FEED, LED PINOUT AND USB ISOLATION

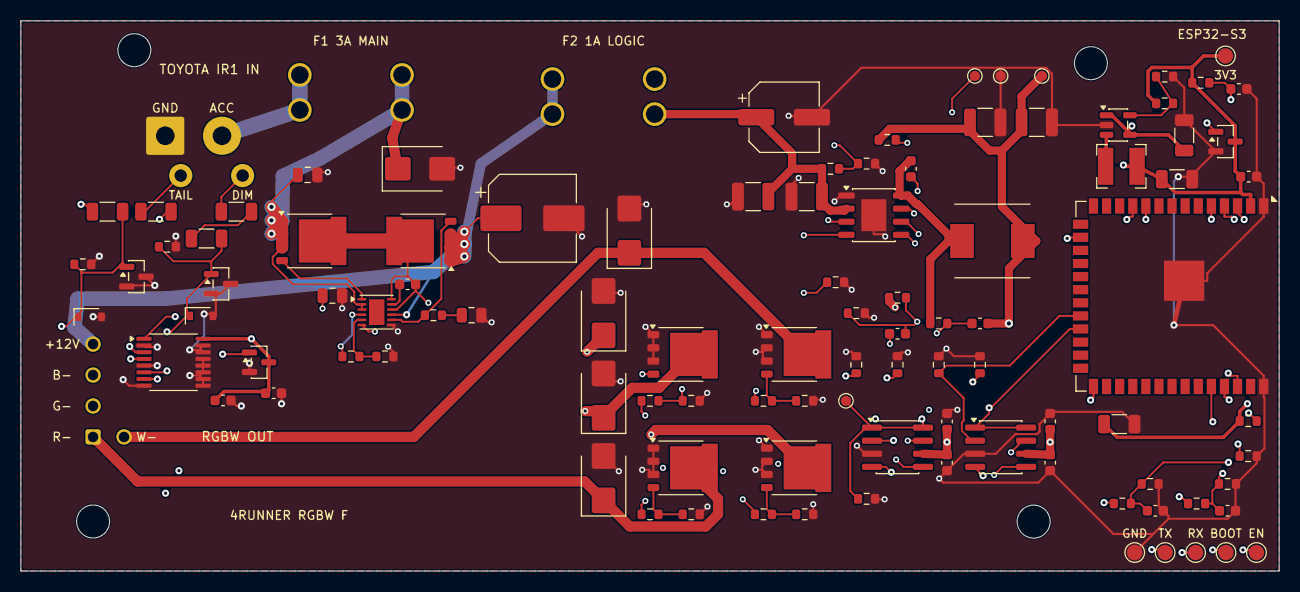
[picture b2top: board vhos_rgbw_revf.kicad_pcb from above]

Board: 4 copper layers, 122.0 x 53.3 mm, 108 parts (0 on the bottom side), 56 nets.

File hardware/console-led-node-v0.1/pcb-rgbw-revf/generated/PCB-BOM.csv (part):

ref,value,mpn,footprint,note,jlcpcb_part
C1,10u 63V EEEFK1J100P,EEEFK1J100P,Capacitor_SMD:CP_Elec_6.3x5.8,"Polar bulk damping candidate; manufacturer 6.3mm diameter, 5.8mm body height. Cable-response/ripple validation pending.",C128459
C2,2.2u 100V X7R,CL32B225KCJVPJE,Capacitor_SMD:C_1210_3225Metric,,C5596903
C3,2.2u 100V X7R,CL32B225KCJVPJE,Capacitor_SMD:C_1210_3225Metric,,C5596903
U1,LM5164QDDARQ1,LM5164QDDARQ1,Package_SO:HSOP-8-1EP_3.9x4.9mm_P1.27mm_EP2.41x3.1mm,"5V logic only; target 0.5A evaluation load, thermal and transient tests pending",C2072225
L1,68u 20% TDK,SPM6545VT-680M-D,VHOS_RevB:TDK_SPM6545VT-D,TDK automotive inductor. Land pattern and maximum envelope from the TDK drawing.,C2047878
R1,39k 1%,0603WAF3902T5E,Resistor_SMD:R_0603_1608Metric,"Uniroyal 0603 thick film, 1%, 0.1 W.",C23153
R2,1M,0603WAF1004T5E,Resistor_SMD:R_0603_1608Metric,"Uniroyal 0603 thick film, 1%, 0.1 W.",C22935
R3,220k 1%,0603WAF2203T5E,Resistor_SMD:R_0603_1608Metric,"Uniroyal 0603 thick film, 1%, 0.1 W.",C22961
R4,150k 1%,0603WAF1503T5E,Resistor_SMD:R_0603_1608Metric,"Uniroyal 0603 thick film, 1%, 0.1 W.",C22807
R5,47k 1%,0603WAF4702T5E,Resistor_SMD:R_0603_1608Metric,"Uniroyal 0603 thick film, 1%, 0.1 W.",C25819
R6,68k 1%,0603WAF6802T5E,Resistor_SMD:R_0603_1608Metric,"Uniroyal 0603 thick film, 1%, 0.1 W.",C23231
C4,2.2n 50V X7R,0603B222K500NT,Capacitor_SMD:C_0603_1608Metric,,C1604
C5,3.3n 50V X7R,CL10B332KB8NNNC,Capacitor_SMD:C_0603_1608Metric,,C1613
C6,180p C0G,CL10C181JB8NNNC,Capacitor_SMD:C_0603_1608Metric,,C17096
C7,22u 25V X7R,MCAST32MSB7226KPNA01,Capacitor_SMD:C_1210_3225Metric,,C5372271
C8,22u 25V X7R,MCAST32MSB7226KPNA01,Capacitor_SMD:C_1210_3225Metric,,C5372271
R7,100k,0603WAF1003T5E,Resistor_SMD:R_0603_1608Metric,"Uniroyal 0603 thick film, 1%, 0.1 W.",C25803
U2,UCC27524AQDRQ1,UCC27524AQDRQ1,Package_SO:SOIC-8_3.9x4.9mm_P1.27mm,5V gate drive; enables have internal pullups overridden by external 2.2k pulldown,C544585
U3,UCC27524AQDRQ1,UCC27524AQDRQ1,Package_SO:SOIC-8_3.9x4.9mm_P1.27mm,5V gate drive; enables have internal pullups overridden by external 2.2k pulldown,C544585
C9,100n 25V X7R,CC0603KRX7R9BB104,Capacitor_SMD:C_0603_1608Metric,,C14663
C11,100n 25V X7R,CC0603KRX7R9BB104,Capacitor_SMD:C_0603_1608Metric,,C14663
C10,1u 25V X7R,CL10B105KA8NNNC,Capacitor_SMD:C_0603_1608Metric,,C29936
C12,1u 25V X7R,CL10B105KA8NNNC,Capacitor_SMD:C_0603_1608Metric,,C29936
R8,2.2k,0603WAF2201T5E,Resistor_SMD:R_0603_1608Metric,"Uniroyal 0603 thick film, 1%, 0.1 W.",C4190
Q1,BUK9Y15-60E,"BUK9Y15-60E,115",Package_TO_SOT_SMD:LFPAK56,"60V; 15mOhm max at 5V gate, 25C. Layout/current ratings remain evaluation targets.",C458196
R9,100,0603WAF1000T5E,Resistor_SMD:R_0603_1608Metric,"Uniroyal 0603 thick film, 1%, 0.1 W.",C22775
R13,10k,0603WAF1002T5E,Resistor_SMD:R_0603_1608Metric,"Uniroyal 0603 thick film, 1%, 0.1 W.",C25804
R17,100k,0603WAF1003T5E,Resistor_SMD:R_0603_1608Metric,"Uniroyal 0603 thick film, 1%, 0.1 W.",C25803
D3,SMBJ24CA,SMBJ24CAQ-13-F,Diode_SMD:D_SMB,Bidirectional output clamp candidate; cable-energy test pending,C1974053
Q2,BUK9Y15-60E,"BUK9Y15-60E,115",Package_TO_SOT_SMD:LFPAK56,"60V; 15mOhm max at 5V gate, 25C. Layout/current ratings remain evaluation targets.",C458196
R10,100,0603WAF1000T5E,Resistor_SMD:R_0603_1608Metric,"Uniroyal 0603 thick film, 1%, 0.1 W.",C22775
R14,10k,0603WAF1002T5E,Resistor_SMD:R_0603_1608Metric,"Uniroyal 0603 thick film, 1%, 0.1 W.",C25804
R18,100k,0603WAF1003T5E,Resistor_SMD:R_0603_1608Metric,"Uniroyal 0603 thick film, 1%, 0.1 W.",C25803
D4,SMBJ24CA,SMBJ24CAQ-13-F,Diode_SMD:D_SMB,Bidirectional output clamp candidate; cable-energy test pending,C1974053
Q3,BUK9Y15-60E,"BUK9Y15-60E,115",Package_TO_SOT_SMD:LFPAK56,"60V; 15mOhm max at 5V gate, 25C. Layout/current ratings remain evaluation targets.",C458196
R11,100,0603WAF1000T5E,Resistor_SMD:R_0603_1608Metric,"Uniroyal 0603 thick film, 1%, 0.1 W.",C22775
R15,10k,0603WAF1002T5E,Resistor_SMD:R_0603_1608Metric,"Uniroyal 0603 thick film, 1%, 0.1 W.",C25804
R19,100k,0603WAF1003T5E,Resistor_SMD:R_0603_1608Metric,"Uniroyal 0603 thick film, 1%, 0.1 W.",C25803
D5,SMBJ24CA,SMBJ24CAQ-13-F,Diode_SMD:D_SMB,Bidirectional output clamp candidate; cable-energy test pending,C1974053
Q4,BUK9Y15-60E,"BUK9Y15-60E,115",Package_TO_SOT_SMD:LFPAK56,"60V; 15mOhm max at 5V gate, 25C. Layout/current ratings remain evaluation targets.",C458196
R12,100,0603WAF1000T5E,Resistor_SMD:R_0603_1608Metric,"Uniroyal 0603 thick film, 1%, 0.1 W.",C22775
R16,10k,0603WAF1002T5E,Resistor_SMD:R_0603_1608Metric,"Uniroyal 0603 thick film, 1%, 0.1 W.",C25804
R20,100k,0603WAF1003T5E,Resistor_SMD:R_0603_1608Metric,"Uniroyal 0603 thick film, 1%, 0.1 W.",C25803
D6,SMBJ24CA,SMBJ24CAQ-13-F,Diode_SMD:D_SMB,Bidirectional output clamp candidate; cable-energy test pending,C1974053
F1,3A MINI MAIN / LED,3568,VHOS_RevB:Keystone_3568_MINI_Vertical,Socket and removable element 0997003.WXN,
F2,1A MINI LOGIC,3568,VHOS_RevB:Keystone_3568_MINI_Vertical,Socket and removable element ATM-1,
U4,LM74800-Q1,LM74800QDRRRQ1,Package_SON:WSON-12-1EP_3x3mm_P0.5mm_EP1.5x2.5mm,Common-drain reverse battery protection and OV cutoff. RTN exposed pad floating.,C3215600
D1,SMBJ28CAQ,SMBJ28CAQ-13-F,Diode_SMD:D_SMB,28 V standoff bidirectional input TVS after the 58 V fuse.,C1975352
Q5,BUK9Y19-100E,"BUK9Y19-100E,115",Package_TO_SOT_SMD:LFPAK56,"100 V reverse-blocking NMOS, source on fused input.",C458229
Q6,BUK9Y19-100E,"BUK9Y19-100E,115",Package_TO_SOT_SMD:LFPAK56,"100 V cutoff NMOS, source on protected output.",C458229
R21,46.4k 0.1%,RT0603BRD0746K4L,Resistor_SMD:R_0603_1608Metric,,C861420
R22,4.02k 0.1%,RT0603BRD074K02L,Resistor_SMD:R_0603_1608Metric,,C705781
R23,100R,0603WAF1000T5E,Resistor_SMD:R_0603_1608Metric,,C22775
C13,100n 100V X7R,CL21B104KCFNNNE,Capacitor_SMD:C_0805_2012Metric,,C28233
C14,100n 100V X7R,CL21B104KCFNNNE,Capacitor_SMD:C_0805_2012Metric,,C28233
C15,100n 50V X7R,CC0603KRX7R9BB104,Capacitor_SMD:C_0603_1608Metric,,C14663
C16,10n 100V X7R,GRM21BR72A103KA01L,Capacitor_SMD:C_0805_2012Metric,,C97925
C17,47u 50V,EEEFK1H470P,Capacitor_SMD:CP_Elec_8x6.2,,C278400
U5,SN3257-Q1,SN3257QPWRQ1,Package_SO:TSSOP-16_4.4x5mm_P0.65mm,A inputs at ground during 3.3 V startup. B inputs selected when the rail supervisor releases.,C1858301
U8,TLV809E 2.93V,TLV809ED29DBZR,Package_TO_SOT_SMD:SOT-23,Keeps both ADC inputs at ground during supply transitions until 3.3 V is valid.,C2864833
R24,49.9k 0.1%,RT1206BRD0749K9L,Resistor_SMD:R_1206_3216Metric,,C706414
R25,49.9k 0.1%,RT1206BRD0749K9L,Resistor_SMD:R_1206_3216Metric,,C706414
R28,22k 0.1%,AT0603BRD0722KL,Resistor_SMD:R_0603_1608Metric,,C5455453
R30,18k 1%,0603WAF1802T5E,Resistor_SMD:R_0603_1608Metric,ADC isolation sets attenuation and keeps GPIO above -0.3 V for a -0.5 V switch output.,C25810
R32,22k 0.1%,AT0603BRD0722KL,Resistor_SMD:R_0603_1608Metric,,C5455453
U6,LM4040 2.5V,LM4040C25QFTA,Package_TO_SOT_SMD:SOT-23,Positive clamp to chassis reference.,C531175
D7,NSVBAT54HT1G,NSVBAT54HT1G,VHOS_RevB:onsemi_SOD-323_477,Negative clamp. Check cold-pulse forward drop on the bench.,C179609
C19,100n 50V,CC0603KRX7R9BB104,Capacitor_SMD:C_0603_1608Metric,,C14663
R26,49.9k 0.1%,RT1206BRD0749K9L,Resistor_SMD:R_1206_3216Metric,,C706414
R27,49.9k 0.1%,RT1206BRD0749K9L,Resistor_SMD:R_1206_3216Metric,,C706414
R29,22k 0.1%,AT0603BRD0722KL,Resistor_SMD:R_0603_1608Metric,,C5455453
R31,18k 1%,0603WAF1802T5E,Resistor_SMD:R_0603_1608Metric,ADC isolation sets attenuation and keeps GPIO above -0.3 V for a -0.5 V switch output.,C25810
R33,22k 0.1%,AT0603BRD0722KL,Resistor_SMD:R_0603_1608Metric,,C5455453
U7,LM4040 2.5V,LM4040C25QFTA,Package_TO_SOT_SMD:SOT-23,Positive clamp to chassis reference.,C531175
D8,NSVBAT54HT1G,NSVBAT54HT1G,VHOS_RevB:onsemi_SOD-323_477,Negative clamp. Check cold-pulse forward drop on the bench.,C179609
C20,100n 50V,CC0603KRX7R9BB104,Capacitor_SMD:C_0603_1608Metric,,C14663
C18,100n 50V,CC0603KRX7R9BB104,Capacitor_SMD:C_0603_1608Metric,,C14663
C21,100n 50V,CC0603KRX7R9BB104,Capacitor_SMD:C_0603_1608Metric,,C14663
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
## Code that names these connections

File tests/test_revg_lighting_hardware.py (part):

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    report = read_json(GENERATED / "electrical-screen.json")
    assert all(report["checks"].values())
    pins = report["native_pin_checks"]
    assert pins["J1"] == {"1": "GND", "2": "VEH_ACC", "3": "TAIL_12V", "4": "DIM_RETURN"}
    assert pins["F1"] == {"1": "VEH_ACC", "2": "ACC_FUSED"}
    assert pins["F2"] == {"1": "LED_POS", "2": "VIN_PROT"}
    assert pins["U4"]["8"] == pins["U4"]["17"] == "EFUSE_RTN"
    assert pins["U4"]["9"] == "GND"
    assert pins["U1"]["5"] == "VIN_PROT"
    assert pins["U11"]["2"] == "ESP_3V3"
    assert [pins["U2"][str(n)] for n in (3, 4, 6, 7)] == [
        "LED_R_NEG", "LED_G_NEG", "LED_B_NEG", "LED_W_NEG",
    ]
    assert pins["D9"] == {"1": "LED_POS", "2": "GND"}
    assert report["driver_disable_logic_high_min_v"] > 2.0
    low, high = report["three_volt_static_v"]
    assert report["max_reset_release_v"] < low < high < 3.6
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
